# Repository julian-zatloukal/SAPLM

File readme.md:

# SAPLM

## Description
SAPLM “Sistema Auxiliar para Personas con Limitaciones Motrices” (English: Auxiliary System for People with Mobility impairments) was a final year project for technical school that aimed to develop a system that helped people with mobility impairments to control appliances and communicate with others by just the use of their voice.

The system itself could be categorized as a home automation system but heavily thought of as an extension of a clinical setup. 

## Project members and involved institutions
The project development and testing was mainly carried out at the school facilities, E.E.S.T. N°9 Prof. Antonio Jose Rodriguez.

Project developers: Da Cruz, Agustín; Villegas, Rocío; Zatloukal Maule, Julián.

Project supervisors: Otero, Diego; Castro, Pujol; Della Paolera, Sergio

## Project Outcome
During all of 2019, from February to the end of November, as a group of three we developed the project and made progress almost every day throughout the year.
The final result allowed the user to use their voice as a trigger of electric appliances such as an electric fan, a bulb, a desk lamp, an electric stove, and even control a small curtain.
The Android application used Google's voice-to-speech API to recognize the user’s speech and send the text to the main board and then fulfill the action.

## Technologies, languages, and programs used
- Mobile Application
  - Android SDK with Java 8 (mobile application)
  - Android Studio
  - Google text-to-speech API
  - Airbnb/epoxy library
- Hardware system
  - AVR GCC (microcontroller’s firmware)
  - Atmel Studio
  - ATmega88PA and ATmega328P
  - CAD Eagle PCB design tool
  - Handmade PCB prototyping
  - Bluetooth Module HC-05
  - 2.4 GFSK connectivity with nRF24L01 module
  - UART and SPI communication
- Project
  - Adobe Illustrator and Adobe Xd
  - Lucid chart	
  - Material IO Icons

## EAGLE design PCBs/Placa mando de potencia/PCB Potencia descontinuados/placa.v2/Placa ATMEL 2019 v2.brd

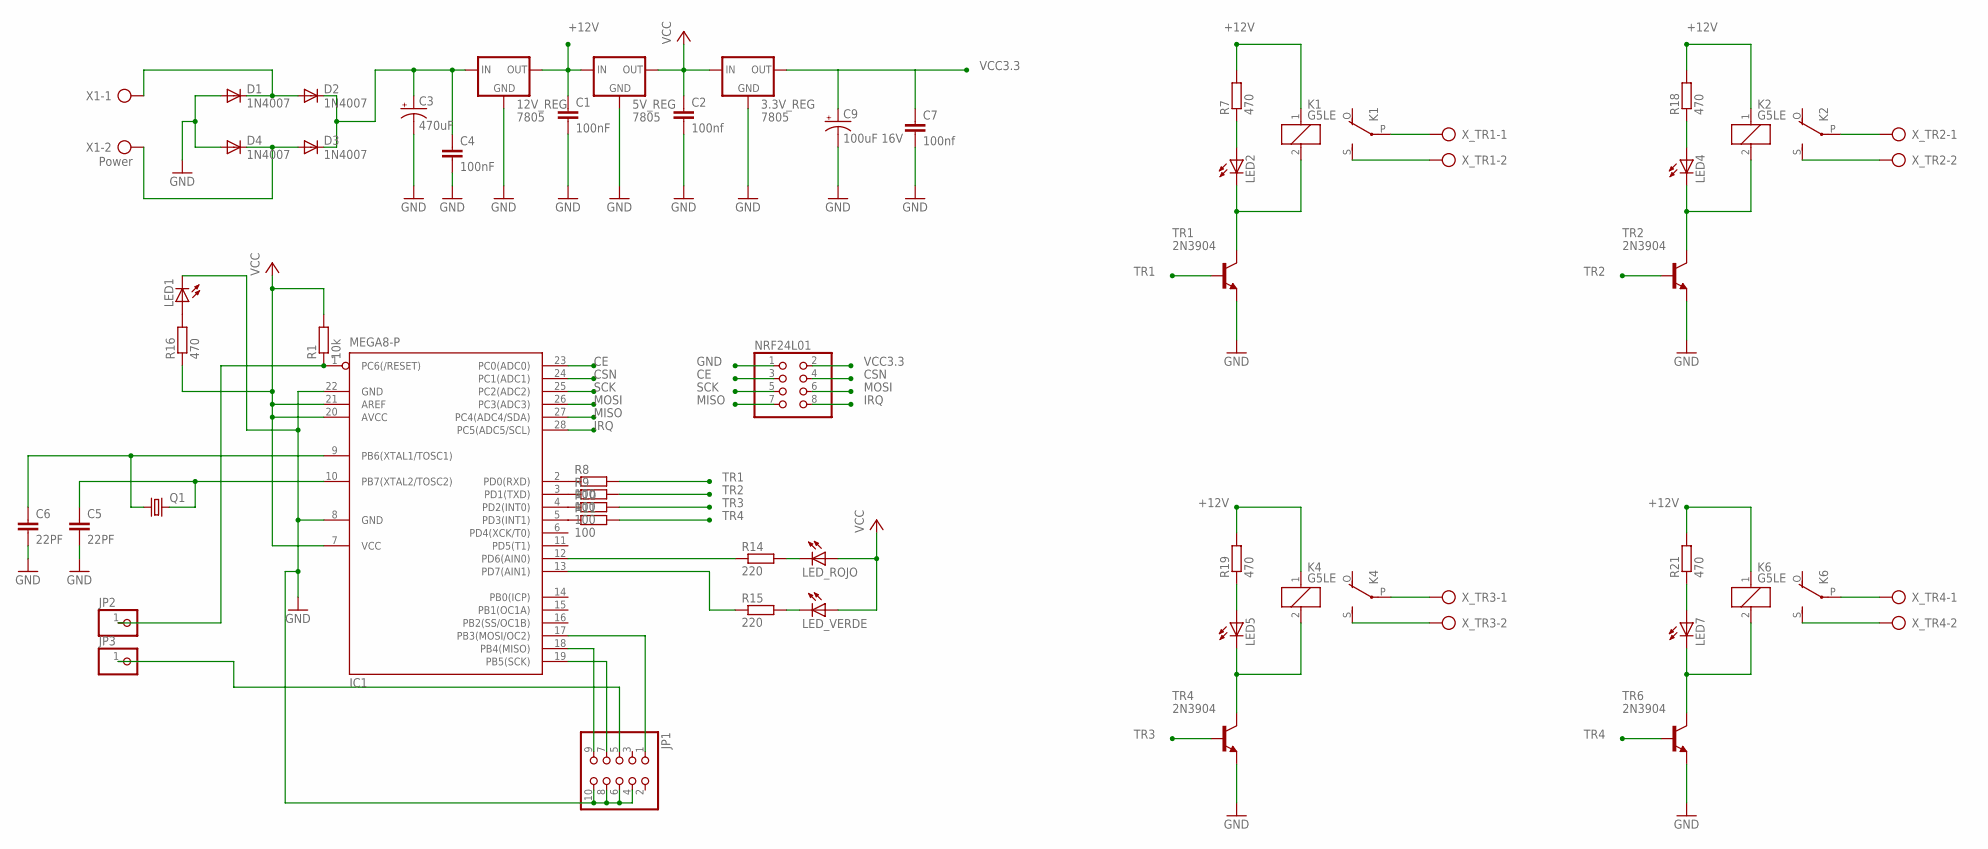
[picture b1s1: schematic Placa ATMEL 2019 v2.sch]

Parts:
3.3V_REG, 5V_REG, 12V_REG: 7805; 78XXL
C1, C4: 100nF; C050-025X075
C2, C7: 100nf; C050-025X075
C3: 470uF; E7,5-16
C5, C6: 22PF; C050-024X044
C9: 100uF 16V; E2,5-7
D1, D2, D3, D4: 1N4007; DO41-10
IC1: MEGA8-P; DIL28-3
JP1: PINHD-2X5; 2X05
JP2, JP3: PINHD-1X1; 1X01
K1, K2, K4, K6: G5LE
LED1, LED2, LED4, LED5, LED7: LED5MM
LED_ROJO: LED5MM
LED_VERDE: LED5MM
NRF24L01: PINHD-2X4; 2X04
Q1: CRYSTALHC49S; HC49/S
R1: 10k; 0207/10
R7, R16, R18, R19, R21: 470; 0309/10
R8, R9, R11: 100; 0207/10
R10: 100; 0207/15
R14, R15: 220; 0207/10
TR1, TR2, TR4, TR6: 2N3904; TO92
X1: Power; AK500/2
X_TR1, X_TR2, X_TR3, X_TR4: AK300/2

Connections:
+12V: 5V_REG.IN, 12V_REG.OUT, C1.1, K1.1, K2.1, K4.1, K6.1, R7.2, R18.2, R19.2, R21.2
CE: IC1.23 (PC0(ADC0)), NRF24L01.3
CSN: IC1.24 (PC1(ADC1)), NRF24L01.4
GND: 3.3V_REG.GND, 5V_REG.GND, 12V_REG.GND, C1.2, C2.2, C3.-, C4.2, C5.2, C6.2, C7.2, C9.-, D1.A, D4.A, IC1.8 (GND), IC1.22 (GND), JP1.4, JP1.6, JP1.8, JP1.10, LED1.K (C), NRF24L01.1, TR1.3 (E), TR2.3 (E), TR4.3 (E), TR6.3 (E)
IRQ: IC1.28 (PC5(ADC5/SCL)), NRF24L01.8
MISO: IC1.27 (PC4(ADC4/SDA)), NRF24L01.7
MOSI: IC1.26 (PC3(ADC3)), NRF24L01.6
unnamed: JP1.5, JP3.1
unnamed: 12V_REG.IN, C3.+, C4.1, D2.C, D3.C
unnamed: K4.S, X_TR3.2
unnamed: K1.S, X_TR1.2
unnamed: K2.S, X_TR2.2
unnamed: LED2.A, R7.1
unnamed: IC1.2 (PD0(RXD)), R8.1
unnamed: IC1.3 (PD1(TXD)), R9.1
unnamed: IC1.4 (PD2(INT0)), R10.1
unnamed: IC1.5 (PD3(INT1)), R11.1
unnamed: LED_ROJO.K (C), R14.2
unnamed: LED_VERDE.K (C), R15.2
unnamed: IC1.12 (PD6(AIN0)), R14.1
unnamed: IC1.13 (PD7(AIN1)), R15.1
unnamed: K6.S, X_TR4.2
unnamed: IC1.17 (PB3(MOSI/OC2)), JP1.1
unnamed: LED1.A, R16.2
unnamed: IC1.19 (PB5(SCK)), JP1.7
unnamed: IC1.18 (PB4(MISO)), JP1.9
unnamed: D1.C, D2.A, X1.1
unnamed: K1.2, LED2.K (C), TR1.1 (C)
unnamed: K1.P, X_TR1.1
unnamed: D3.A, D4.C, X1.2
unnamed: LED4.A, R18.1
unnamed: K2.2, LED4.K (C), TR2.1 (C)
unnamed: K2.P, X_TR2.1
unnamed: LED5.A, R19.1
unnamed: K4.2, LED5.K (C), TR4.1 (C)
unnamed: K4.P, X_TR3.1
unnamed: IC1.1 (PC6(/RESET)), JP2.1, R1.1
unnamed: LED7.A, R21.1
unnamed: C5.1, IC1.10 (PB7(XTAL2/TOSC2)), Q1.2
unnamed: C6.1, IC1.9 (PB6(XTAL1/TOSC1)), Q1.1
unnamed: K6.2, LED7.K (C), TR6.1 (C)
unnamed: K6.P, X_TR4.1
SCK: IC1.25 (PC2(ADC2)), NRF24L01.5
TR1: R8.2, TR1.2 (B)
TR2: R9.2, TR2.2 (B)
TR3: R10.2, TR4.2 (B)
TR4: R11.2, TR6.2 (B)
VCC: 3.3V_REG.IN, 5V_REG.OUT, C2.1, IC1.7 (VCC), IC1.20 (AVCC), IC1.21 (AREF), LED_ROJO.A, LED_VERDE.A, R1.2, R16.1
VCC3.3: 3.3V_REG.OUT, C7.1, C9.+, NRF24L01.2

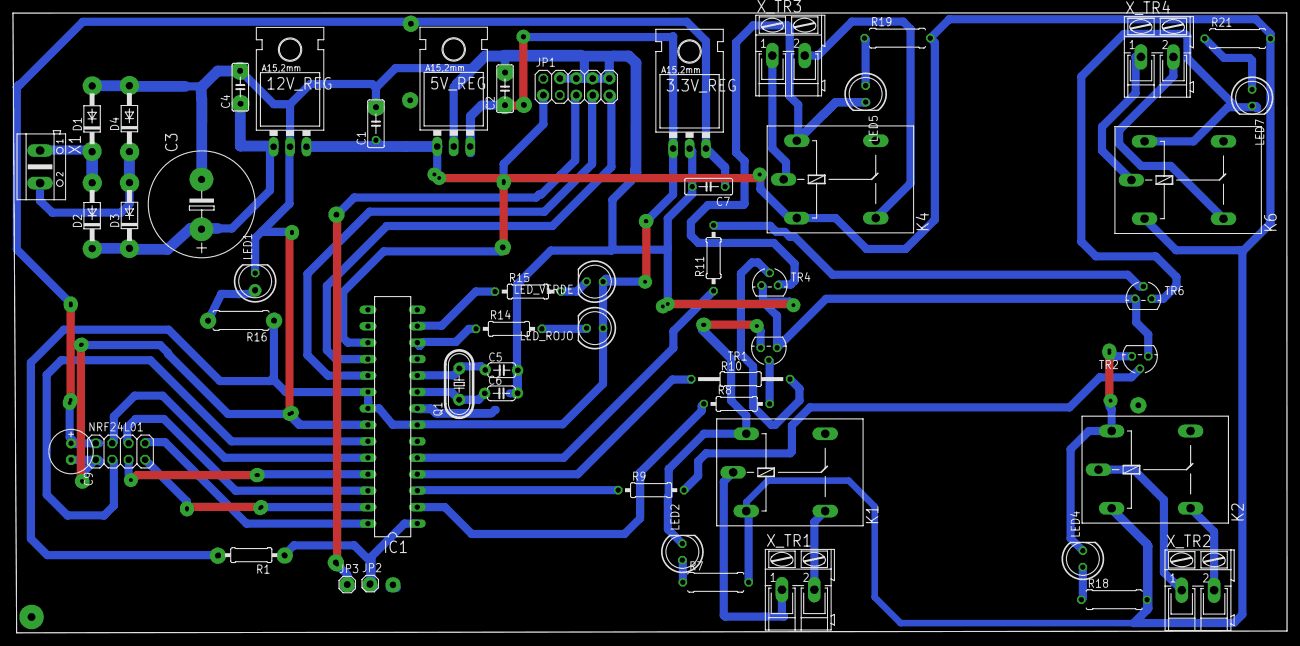
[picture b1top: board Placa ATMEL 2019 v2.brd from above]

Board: 2 copper layers, 196.7 x 95.7 mm, 53 parts (0 on the bottom side), 49 nets.

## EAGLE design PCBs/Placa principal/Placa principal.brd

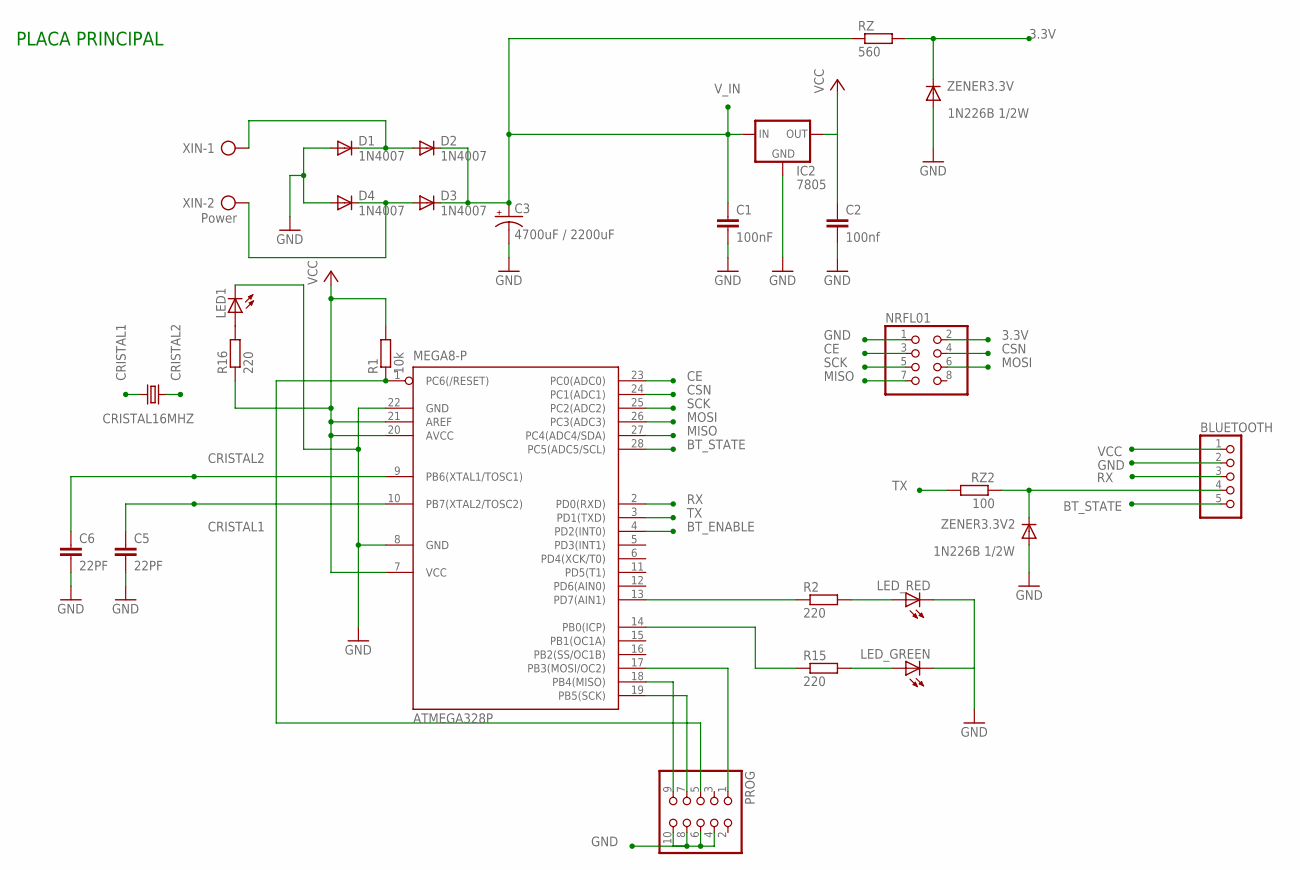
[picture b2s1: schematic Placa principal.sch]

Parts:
ATMEGA328P: MEGA8-P; DIL28-3
BLUETOOTH: PINHD-1X5; 1X05
C1: 100nF; C050-025X075
C2: 100nf; C050-025X075
C3: 4700uF / 2200uF; E7,5-16
C5, C6: 22PF; C050-024X044
CRISTAL16MHZ: CRYSTALHC49S; HC49/S
D1, D2, D3, D4: 1N4007; DO41-10
IC2: 7805; 78XXL
LED1: LED5MM
LED_GREEN: LED5MM
LED_RED: LED5MM
NRFL01: PINHD-2X4; 2X04
PROG: PINHD-2X5; 2X05
R1: 10k; 0207/10
R2, R15: 220; 0207/10
R16: 220; 0309/10
RZ: 560; 0207/10
RZ2: 100; 0207/10
XIN: Power; AK500/2
ZENER3.3V, ZENER3.3V2: 1N226B 1/2W; DO35-10

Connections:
3.3V: NRFL01.2, RZ.2, ZENER3.3V.C
BT_ENABLE: ATMEGA328P.4 (PD2(INT0))
BT_STATE: ATMEGA328P.28 (PC5(ADC5/SCL)), BLUETOOTH.5
CE: ATMEGA328P.23 (PC0(ADC0)), NRFL01.3
CRISTAL1: ATMEGA328P.10 (PB7(XTAL2/TOSC2)), C5.1, CRISTAL16MHZ.2
CRISTAL2: ATMEGA328P.9 (PB6(XTAL1/TOSC1)), C6.1, CRISTAL16MHZ.1
CSN: ATMEGA328P.24 (PC1(ADC1)), NRFL01.4
GND: ATMEGA328P.8 (GND), ATMEGA328P.22 (GND), BLUETOOTH.2, C1.2, C2.2, C3.-, C5.2, C6.2, D1.A, D4.A, IC2.GND, LED1.K (C), LED_GREEN.K (C), LED_RED.K (C), NRFL01.1, PROG.4, PROG.6, PROG.8, PROG.10, ZENER3.3V.A, ZENER3.3V2.A
MISO: ATMEGA328P.27 (PC4(ADC4/SDA)), NRFL01.7
MOSI: ATMEGA328P.26 (PC3(ADC3)), NRFL01.6
unnamed: ATMEGA328P.1 (PC6(/RESET)), PROG.5, R1.1
unnamed: LED_RED.A, R2.2
unnamed: ATMEGA328P.14 (PB0(ICP)), R15.1
unnamed: ATMEGA328P.13 (PD7(AIN1)), R2.1
unnamed: ATMEGA328P.17 (PB3(MOSI/OC2)), PROG.1
unnamed: LED1.A, R16.2
unnamed: ATMEGA328P.19 (PB5(SCK)), PROG.7
unnamed: ATMEGA328P.18 (PB4(MISO)), PROG.9
unnamed: D1.C, D2.A, XIN.1
unnamed: BLUETOOTH.4, RZ2.1, ZENER3.3V2.C
unnamed: D3.A, D4.C, XIN.2
unnamed: LED_GREEN.A, R15.2
RX: ATMEGA328P.2 (PD0(RXD)), BLUETOOTH.3
SCK: ATMEGA328P.25 (PC2(ADC2)), NRFL01.5
TX: ATMEGA328P.3 (PD1(TXD)), RZ2.2
VCC: ATMEGA328P.7 (VCC), ATMEGA328P.20 (AVCC), ATMEGA328P.21 (AREF), BLUETOOTH.1, C2.1, IC2.OUT, R1.2, R16.1
V_IN: C1.1, C3.+, D2.C, D3.C, IC2.IN, RZ.1

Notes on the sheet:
PLACA PRINCIPAL

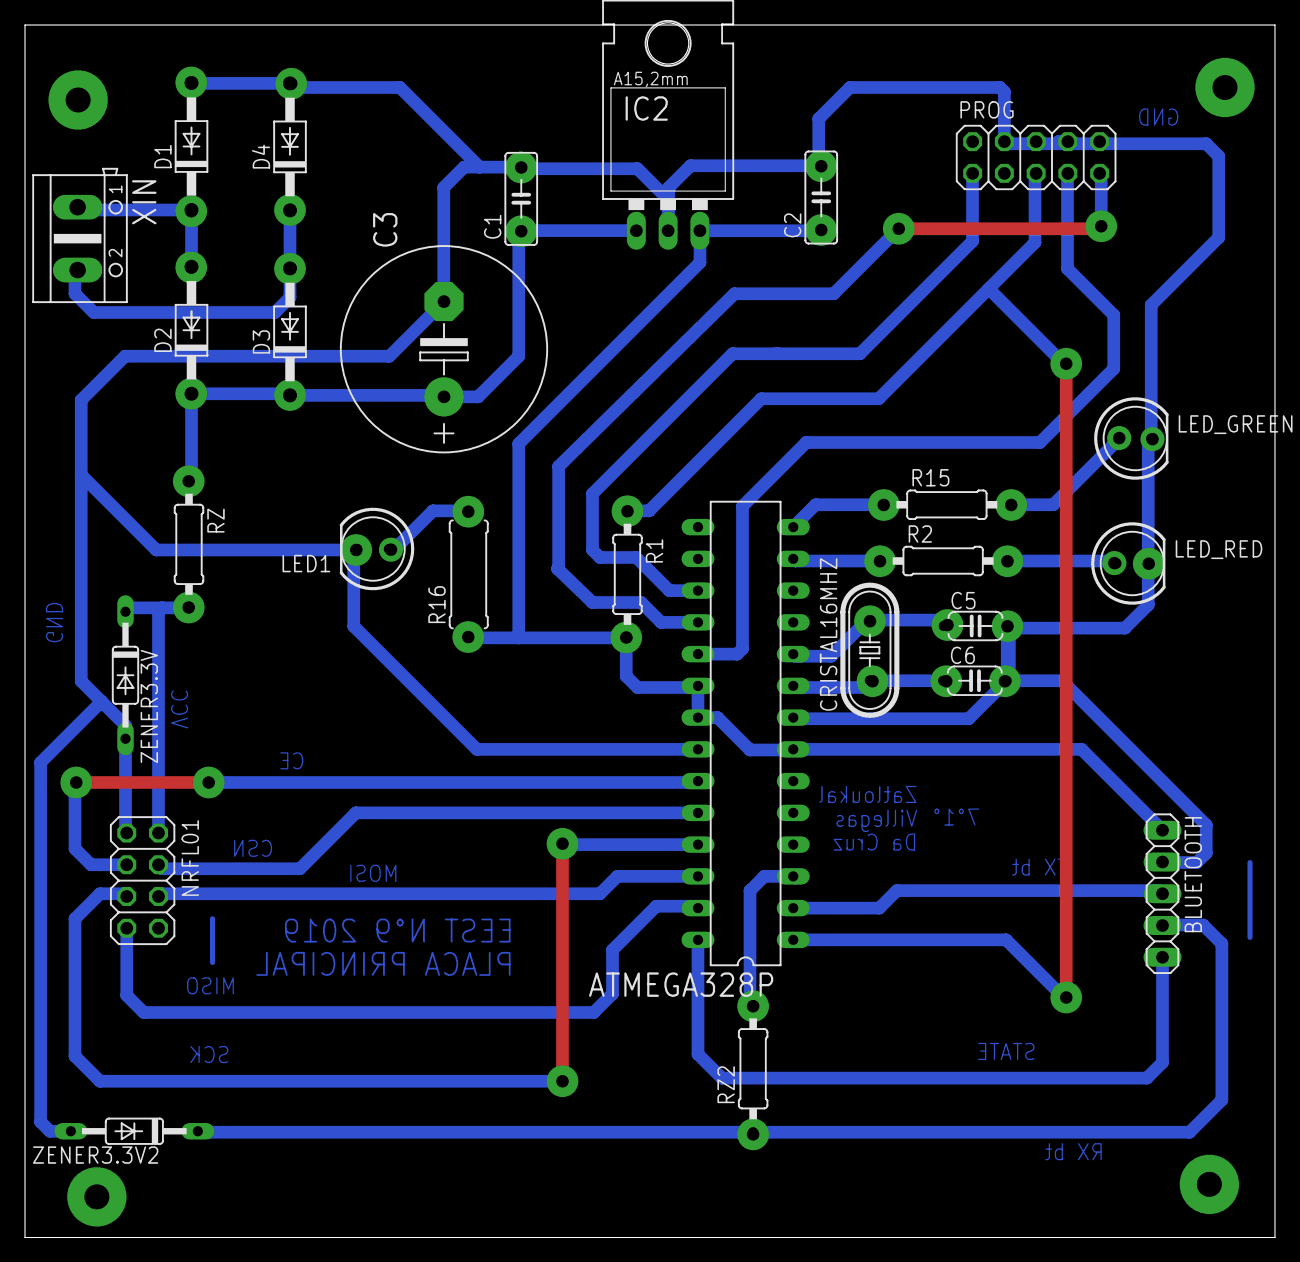
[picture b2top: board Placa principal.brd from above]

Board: 2 copper layers, 100.0 x 97.0 mm, 27 parts (0 on the bottom side), 26 nets.

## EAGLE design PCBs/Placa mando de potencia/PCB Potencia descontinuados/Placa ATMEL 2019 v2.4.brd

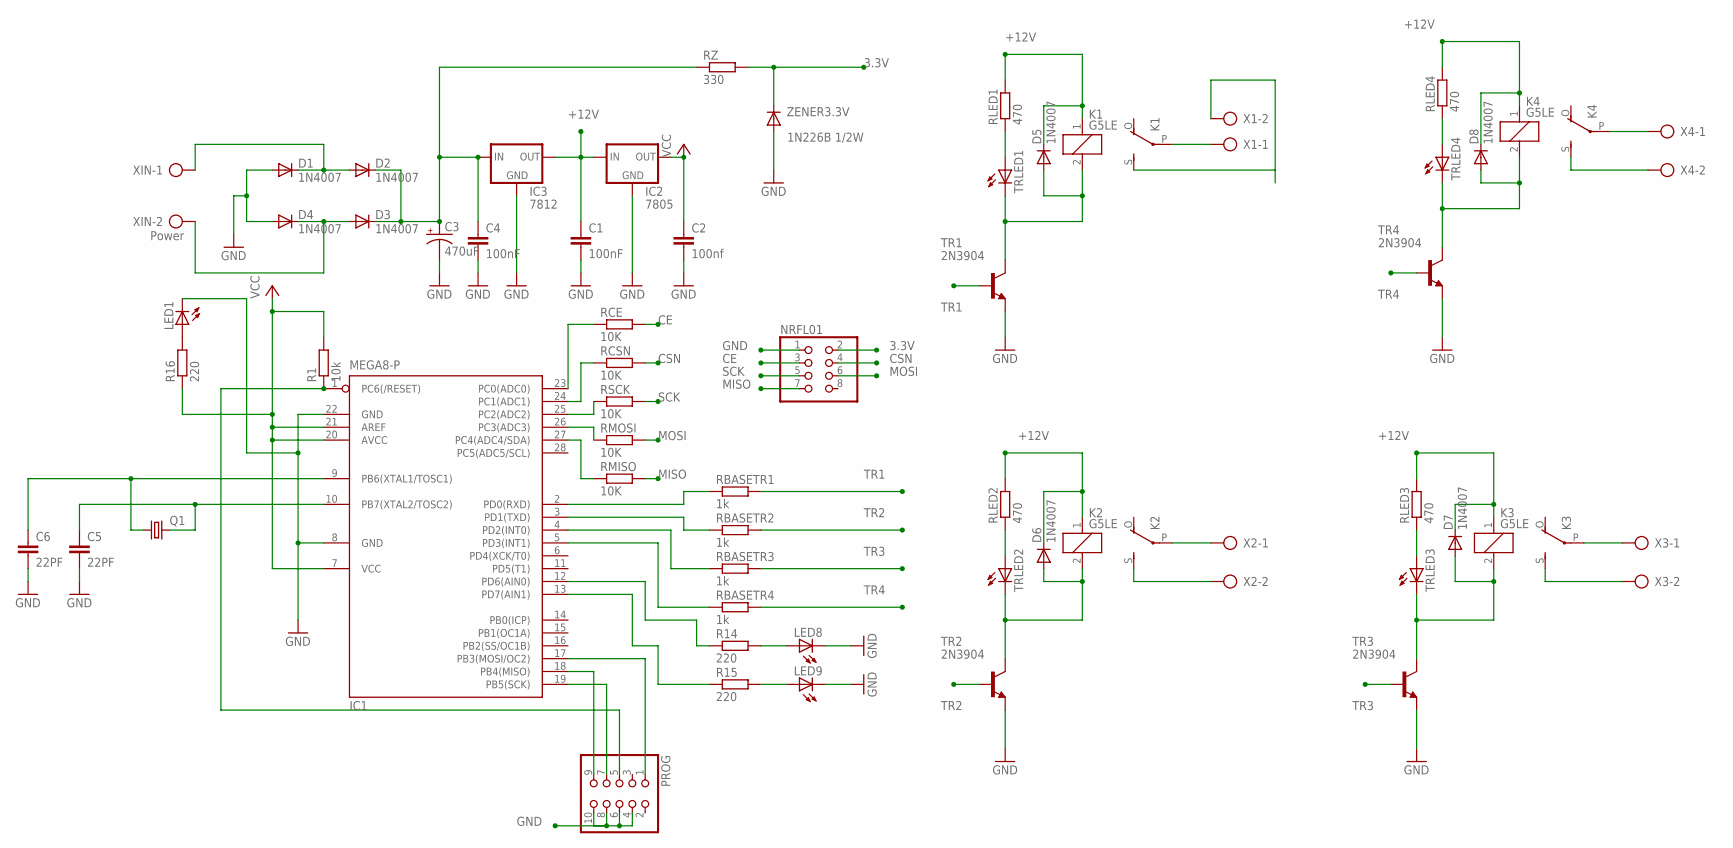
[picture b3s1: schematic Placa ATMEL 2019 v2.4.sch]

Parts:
C1, C4: 100nF; C050-025X075
C2: 100nf; C050-025X075
C3: 470uF; E7,5-16
C5, C6: 22PF; C050-024X044
D1, D2, D3, D4, D5, D6, D7, D8: 1N4007; DO41-10
IC1: MEGA8-P; DIL28-3
IC2: 7805; 78XXL
IC3: 7812; 78XXL
K1, K2, K3, K4: G5LE
LED1, LED8, LED9: LED5MM
NRFL01: PINHD-2X4; 2X04
PROG: PINHD-2X5; 2X05
Q1: CRYSTALHC49S; HC49/S
R1: 10k; 0207/10
R14, R15: 220; 0207/10
R16: 220; 0309/10
RBASETR1, RBASETR2: 1k; 0207/10
RBASETR3: 1k; 0204/7
RBASETR4: 1k; 0207/15
RCE: 10K; 0207/10
RCSN: 10K; 0207/10
RLED1, RLED2, RLED3, RLED4: 470; 0207/10
RMISO: 10K; 0207/10
RMOSI: 10K; 0207/10
RSCK: 10K; 0207/10
RZ: 330; 0207/10
TR1, TR2, TR3, TR4: 2N3904; TO92
TRLED1, TRLED2, TRLED3, TRLED4: LED5MM
X1, X2, X3, X4: AK300/2
XIN: Power; AK500/2
ZENER3.3V: 1N226B 1/2W; DO35-10

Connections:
3.3V: NRFL01.2, RZ.2, ZENER3.3V.C
+12V: C1.1, D5.C, D6.C, D7.C, D8.C, IC2.IN, IC3.OUT, K1.1, K2.1, K3.1, K4.1, RLED1.2, RLED2.2, RLED3.2, RLED4.2
CE: NRFL01.3, RCE.2
CSN: NRFL01.4, RCSN.2
GND: C1.2, C2.2, C3.-, C4.2, C5.2, C6.2, D1.A, D4.A, IC1.8 (GND), IC1.22 (GND), IC2.GND, IC3.GND, LED1.K (C), LED8.K (C), LED9.K (C), NRFL01.1, PROG.4, PROG.6, PROG.8, PROG.10, TR1.3 (E), TR2.3 (E), TR3.3 (E), TR4.3 (E), ZENER3.3V.A
MISO: NRFL01.7, RMISO.2
MOSI: NRFL01.6, RMOSI.2
unnamed: IC1.1 (PC6(/RESET)), PROG.5, R1.1
unnamed: IC1.23 (PC0(ADC0)), RCE.1
unnamed: IC1.24 (PC1(ADC1)), RCSN.1
unnamed: IC1.25 (PC2(ADC2)), RSCK.1
unnamed: IC1.26 (PC3(ADC3)), RMOSI.1
unnamed: RLED1.1, TRLED1.A
unnamed: IC1.2 (PD0(RXD)), RBASETR1.1
unnamed: IC1.3 (PD1(TXD)), RBASETR2.1
unnamed: IC1.4 (PD2(INT0)), RBASETR3.1
unnamed: IC1.5 (PD3(INT1)), RBASETR4.1
unnamed: IC1.12 (PD6(AIN0)), R14.1
unnamed: IC1.13 (PD7(AIN1)), R15.1
unnamed: IC1.27 (PC4(ADC4/SDA)), RMISO.1
unnamed: IC1.17 (PB3(MOSI/OC2)), PROG.1
unnamed: LED1.A, R16.2
unnamed: IC1.19 (PB5(SCK)), PROG.7
unnamed: IC1.18 (PB4(MISO)), PROG.9
unnamed: C3.+, C4.1, D2.C, D3.C, IC3.IN, RZ.1
unnamed: D1.C, D2.A, XIN.1
unnamed: D5.A, K1.2, TR1.1 (C), TRLED1.K (C)
unnamed: K1.S, X1.2
unnamed: K1.P, X1.1
unnamed: D3.A, D4.C, XIN.2
unnamed: RLED2.1, TRLED2.A
unnamed: D6.A, K2.2, TR2.1 (C), TRLED2.K (C)
unnamed: K2.S, X2.2
unnamed: K2.P, X2.1
unnamed: RLED3.1, TRLED3.A
unnamed: D7.A, K3.2, TR3.1 (C), TRLED3.K (C)
unnamed: K3.S, X3.2
unnamed: K3.P, X3.1
unnamed: RLED4.1, TRLED4.A
unnamed: C5.1, IC1.10 (PB7(XTAL2/TOSC2)), Q1.2
unnamed: C6.1, IC1.9 (PB6(XTAL1/TOSC1)), Q1.1
unnamed: D8.A, K4.2, TR4.1 (C), TRLED4.K (C)
unnamed: K4.S, X4.2
unnamed: K4.P, X4.1
unnamed: LED8.A, R14.2
unnamed: LED9.A, R15.2
SCK: NRFL01.5, RSCK.2
TR1: RBASETR1.2, TR1.2 (B)
TR2: RBASETR2.2, TR2.2 (B)
TR3: RBASETR3.2, TR3.2 (B)
TR4: RBASETR4.2, TR4.2 (B)
VCC: C2.1, IC1.7 (VCC), IC1.20 (AVCC), IC1.21 (AREF), IC2.OUT, R1.2, R16.1

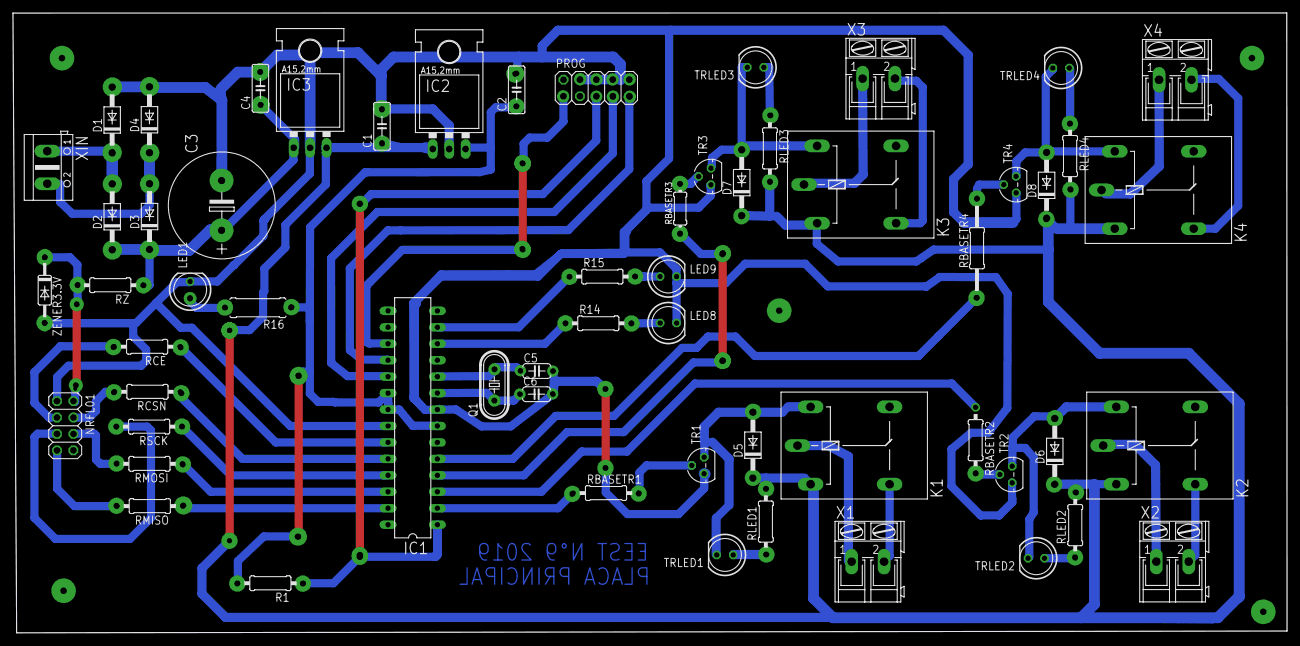
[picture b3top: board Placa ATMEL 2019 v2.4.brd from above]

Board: 2 copper layers, 196.7 x 95.7 mm, 59 parts (0 on the bottom side), 52 nets.

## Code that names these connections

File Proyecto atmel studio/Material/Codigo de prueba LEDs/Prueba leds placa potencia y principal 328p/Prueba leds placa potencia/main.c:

#define F_CPU 16000000UL

#define bit_get(p,m) ((p) & (m))
#define bit_set(p,m) ((p) |= (m))
#define bit_clear(p,m) ((p) &= ~(m))
#define bit_flip(p,m) ((p) ^= (m))
#define bit_write(c,p,m) (c ? bit_set(p,m) : bit_clear(p,m))
#define BIT(x) (0x01 << (x))
#define LONGBIT(x) ((unsigned long)0x00000001 << (x))
#include <avr/io.h>
#include <util/delay.h>

void initIO();

int main(void)
{
	initIO();

    while (1) 
    {
		bit_flip(PORTD, BIT(7));
		bit_flip(PORTB, BIT(0));
		_delay_ms(1000);
    }
}

void initIO(){
	/*	
		Input/Output pin initialization
		1 : OUTPUT | 0 : INPUT | 0b76543210 Bit order
		ATTACHMENTS
			RELAY 0		: PD3				|	OUTPUT
			RELAY 1		: PD2				|	OUTPUT
			RELAY 2		: PD6				|	OUTPUT
			RELAY 3		: PD5				|	OUTPUT
			GREEN LED	: PD7				|	OUTPUT
			RED LED		: PB0				|	OUTPUT
		nRF24L01
			CE	 : PC0						|	OUTPUT
			CSN	 : PC1						|	OUTPUT
			MISO : PD0 (MSPIM MISO ATMEGA)	|	INPUT
			MOSI : PD1 (MSPIM MOSI ATMEGA)	|	OUTPUT
			SCK	 : PD4 (MSPIM XCK)			|	OUTPUT
	*/ 
	DDRD = 0b11111110;
	DDRB = 0b00101001;
	DDRC = 0b11011111;
}

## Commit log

2021-03-22 Add readme
2021-03-22 Change logo
2021-03-22 Change wording
2021-03-22 Clean folders
2021-03-22 Create LICENSE
